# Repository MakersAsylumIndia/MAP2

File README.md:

# MAP2

**Maker's Asylum Project #2**

"learn to solder kit, through hole, interactive art"

1. 1 LDR, 1 LED, 1 Transistor and a few passives. 10 parts in all.
2. 1 inch square board
3. Build many and create a matrix for interactive art.

DISCUSSION FORUM : https://github.com/MakersAsylumIndia/MAP2

Through Hole Version

SMD + Through Hole Version (MAP2_smd)

License
-------
[CERN Open Hardware Licence v1.2 ]

[CERN Open Hardware Licence v1.2 ]:http://www.ohwr.org/attachments/2388/cern_ohl_v_1_2.txt

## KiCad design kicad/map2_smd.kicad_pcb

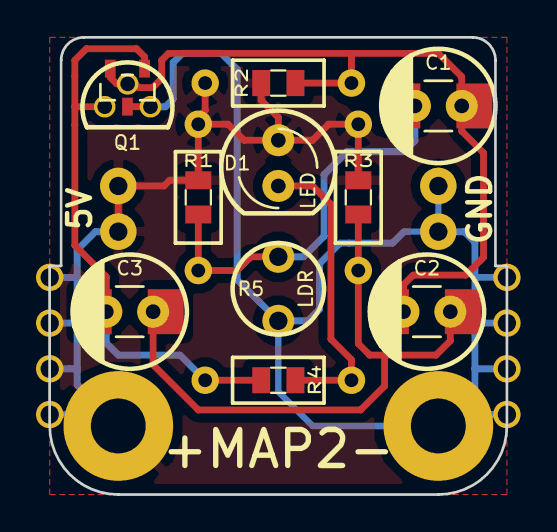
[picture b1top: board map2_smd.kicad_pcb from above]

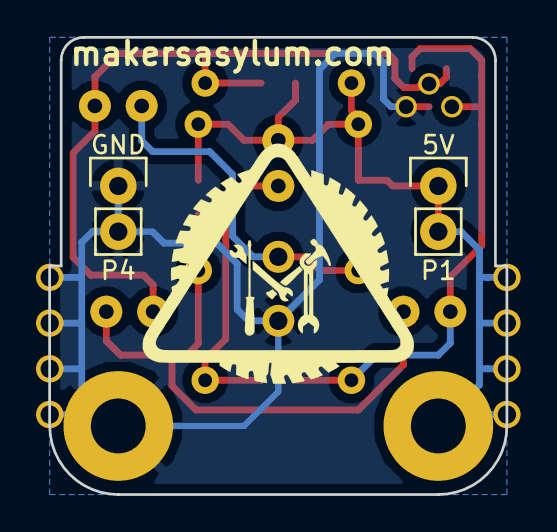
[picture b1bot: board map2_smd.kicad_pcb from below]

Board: 2 copper layers, 25.4 x 25.4 mm, 23 parts (3 on the bottom side), 7 nets.

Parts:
C1: 100uF; C_1210
C2, C3: 47uF; C_1210
D1: LED; LED-5MM
P1: 5V; Pin_Header_Straight_1x02
P4: GND; Pin_Header_Straight_1x02
P7, P8: MTG; MTG_3mm
P9: LOGO; MA_LOGO
Q1: 2N2222; sot23
R1: 2k2; r_0805
R2: 1M; r_0805
R3: 3k3; r_0805
R4: 270E; r_0805
R5: LDR; R_photo
via1, via1#2, via1#3, via1#4, via2, via2#2, via2#3, via2#4: via

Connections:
/5V: D1.1, P1.1, P1.2, P8.1, R1.1, R2.1, R3.1, via2.1, via2#2.1, via2#3.1, via2#4.1
/BASE: C1.1, C2.2, Q1.2, R2.2
/COLL: C3.2, Q1.1, R4.2
/GND: P4.1, P4.2, P7.1, Q1.3, R5.2, via1.1, via1#2.1, via1#3.1, via1#4.1
/LDR: C1.2, R1.2, R5.1
/LED: D1.2, R4.1
unnamed: C2.1, C3.1, R3.2

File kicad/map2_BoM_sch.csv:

Reference, Value, Footprint, Datasheet, Field4, Field5, Field6, Field7, Field8, Field9, Field10, Field11
R1,2k2,map2:Resistor_Horizontal_RM10mm,
R2,1M,map2:Resistor_Horizontal_RM10mm,
R3,3k3,map2:Resistor_Horizontal_RM10mm,
R4,270E,map2:Resistor_Horizontal_RM10mm,
D1,LED,map2:LED-5MM,,LED SS 5MM 625NM RED DIFF,2V, 10mA,Round with Domed Top, 5mm, T-1 3/4,Kingbright Corp,WP7113ID,Digikey,754-1264-ND,http://www.digikey.com/product-detail/en/WP7113ID/754-1264-N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
C1,100uF,map2:Capacitor5x6RM2.5,,CAP ALUM 100UF 16V 20% RADIAL,100u,16V,Radial, Can, 6.3mm dia,Panasonic Electronic Components,ECE-A1CKA101,Digikey,P833-ND,http://www.digikey.com/product-detail/en/ECE-A1CKA101/P833-N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
C2,47uF,map2:Capacitor5x6RM2.5,,CAP ALUM 100UF 16V 20% RADIAL,100u,16V,Radial, Can, 6.3mm dia,Panasonic Electronic Components,ECE-A1CKA101,Digikey,P833-ND,http://www.digikey.com/product-detail/en/ECE-A1CKA101/P833-N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
C3,47uF,map2:Capacitor5x6RM2.5,,CAP ALUM 100UF 16V 20% RADIAL,100u,16V,Radial, Can, 6.3mm dia,Panasonic Electronic Components,ECE-A1CKA101,Digikey,P833-ND,http://www.digikey.com/product-detail/en/ECE-A1CKA101/P833-N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
Q1,2N2222,map2:TO-92-Bipolar-rugged-CBE,
P2,5V,map2:Pin_Header_Straight_1x01,
P5,GND,map2:Pin_Header_Straight_1x01,
P7,MTG,map2:MountingHole_3mm,
P8,MTG,map2:MountingHole_3mm,
P9,LOGO,,
P1,5V,map2:Pin_Header_Straight_1x01,
P4,GND,map2:Pin_Header_Straight_1x01,
BT1,CR2032,,,HOLDER BATTERY COIN 20MM DIA THM,Coin Cell, Retainer,Coin, 20.0mm,Keystone Electronics,3003,Digikey,3003K-ND,http://www.digikey.com/scripts/DkSearch/dksus.dll?x=0&y=0&la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
R5,R_photo,map2:R_photo,

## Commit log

2016-02-27 learn to solder kit for Maker's Asylum
2016-02-27 work in progress
2016-02-28 gerbers ready
2016-02-29 added gerbers, BoM, images
2016-03-01 added _smd version
2016-03-02 _smd version gerbers
2016-03-02 gerbers ready for MAP2_smd
2016-03-03 working on 3D cad layout
2016-03-16 added PCBpower PI
2016-03-25 added pictures of boards and assembly
2017-10-14 base drilling template added
